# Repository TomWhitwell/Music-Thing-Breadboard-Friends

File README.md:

# Music Thing Breadboard Friends

Just a eurorack socket board for Thonkiconn and Stereo Thonkiconn sockets so far 

Space for two Mono and two Stereo sockets

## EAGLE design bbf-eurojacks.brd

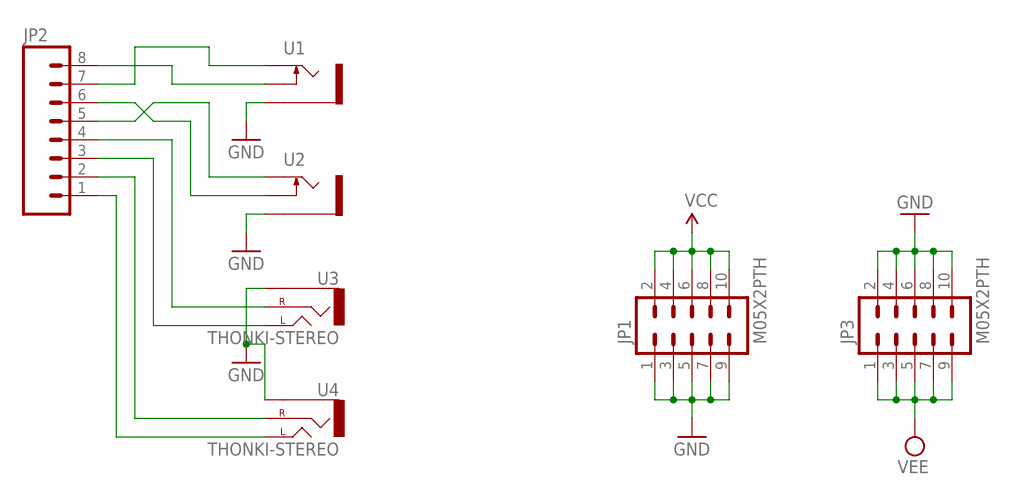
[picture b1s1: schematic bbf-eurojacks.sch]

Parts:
JP1, JP3: M05X2PTH; AVR_ICSP
JP2: M08; 1X08
U1, U2: THONKICONNNEW; WQP-PJ301M-12_JACK
U3, U4: THONKI-STEREO; WQP-PJ366ST_JACK

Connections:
2-SWITCH: JP2.6, U2.P$2_SWITCH (SWITCH)
2-TIP: JP2.5, U2.P$1_TIP (TIP)
3-LEFT: JP2.3, U3.P$1_TIP (LEFT)
3-RIGHT: JP2.4, U3.P$2_SWITCH (RIGHT)
4-LEFT: JP2.1, U4.P$1_TIP (LEFT)
4-RIGHT: JP2.2, U4.P$2_SWITCH (RIGHT)
GND: JP1.1, JP1.3, JP1.5, JP1.7, JP1.9, JP3.2, JP3.4, JP3.6, JP3.8, JP3.10, U1.P$3_SLEEVE (SLEEVE), U2.P$3_SLEEVE (SLEEVE), U3.P$3_SLEEVE (SLEEVE), U4.P$3_SLEEVE (SLEEVE)
unnamed: JP2.8, U1.P$2_SWITCH (SWITCH)
unnamed: JP2.7, U1.P$1_TIP (TIP)
VCC: JP1.2, JP1.4, JP1.6, JP1.8, JP1.10
VEE: JP3.1, JP3.3, JP3.5, JP3.7, JP3.9

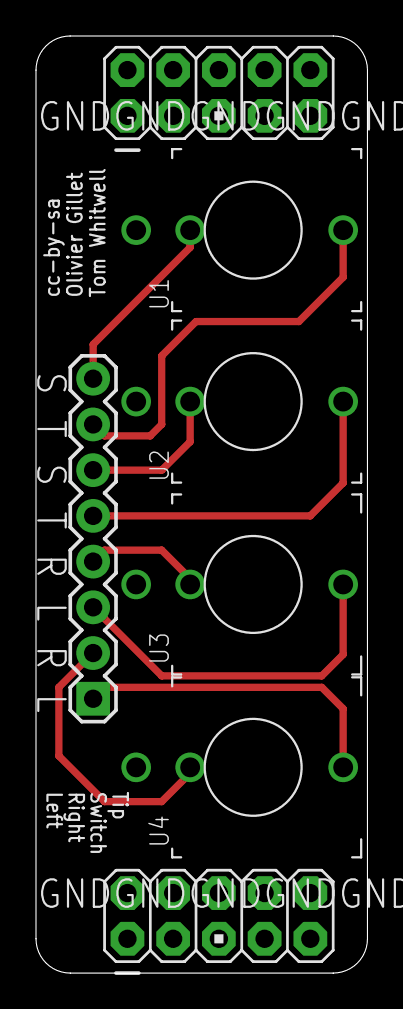
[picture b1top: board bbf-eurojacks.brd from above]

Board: 2 copper layers, 18.4 x 52.1 mm, 7 parts (0 on the bottom side), 11 nets.

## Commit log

2018-01-17 upload first test version

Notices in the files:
bbf-eurojacks.brd:
cc-by-sa
